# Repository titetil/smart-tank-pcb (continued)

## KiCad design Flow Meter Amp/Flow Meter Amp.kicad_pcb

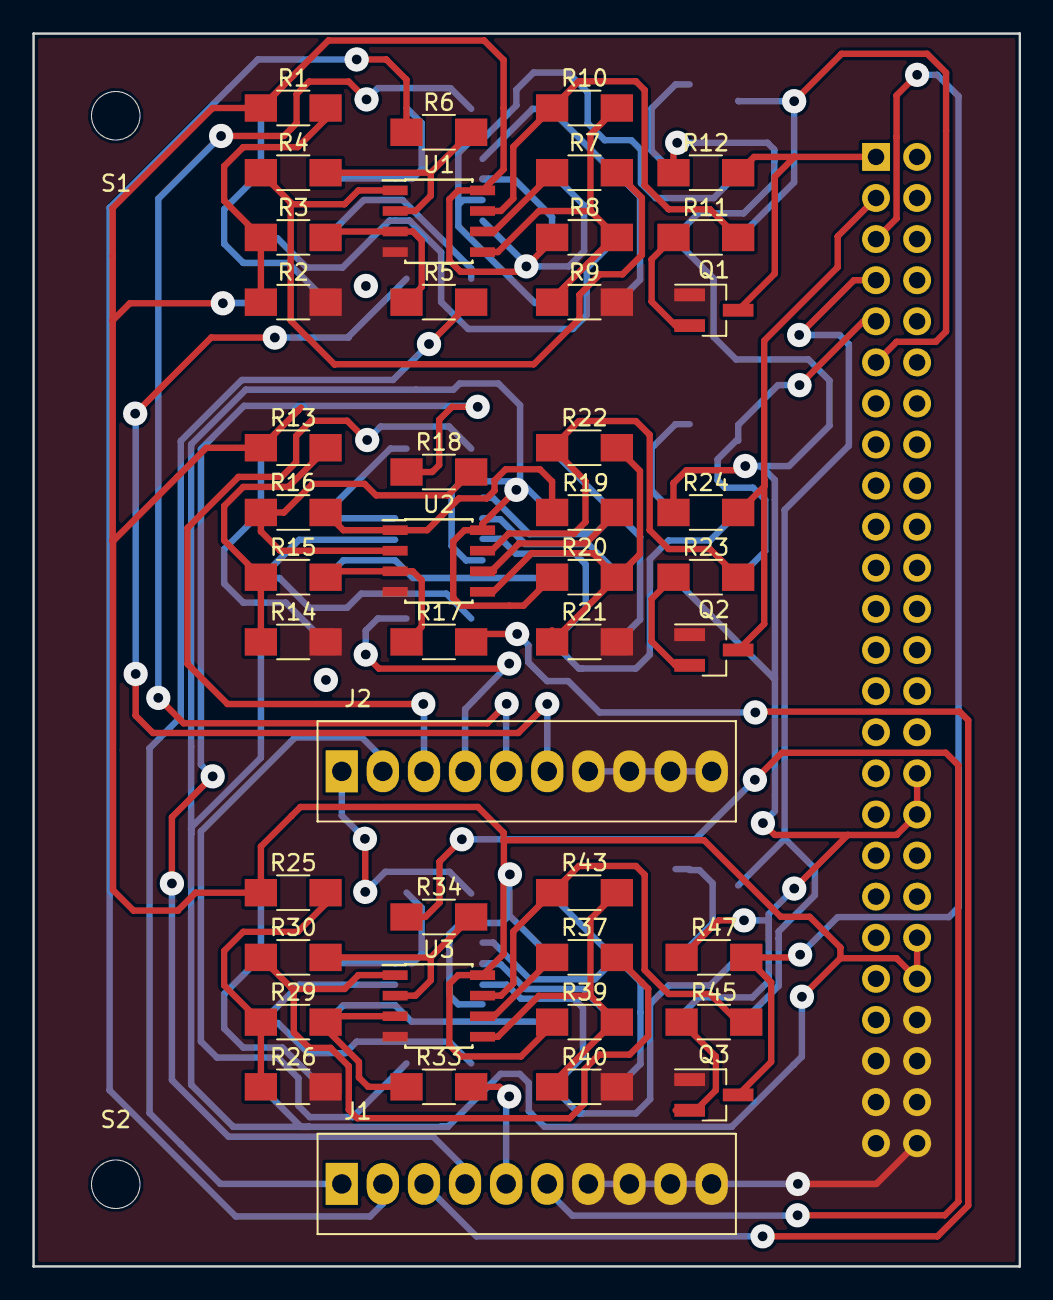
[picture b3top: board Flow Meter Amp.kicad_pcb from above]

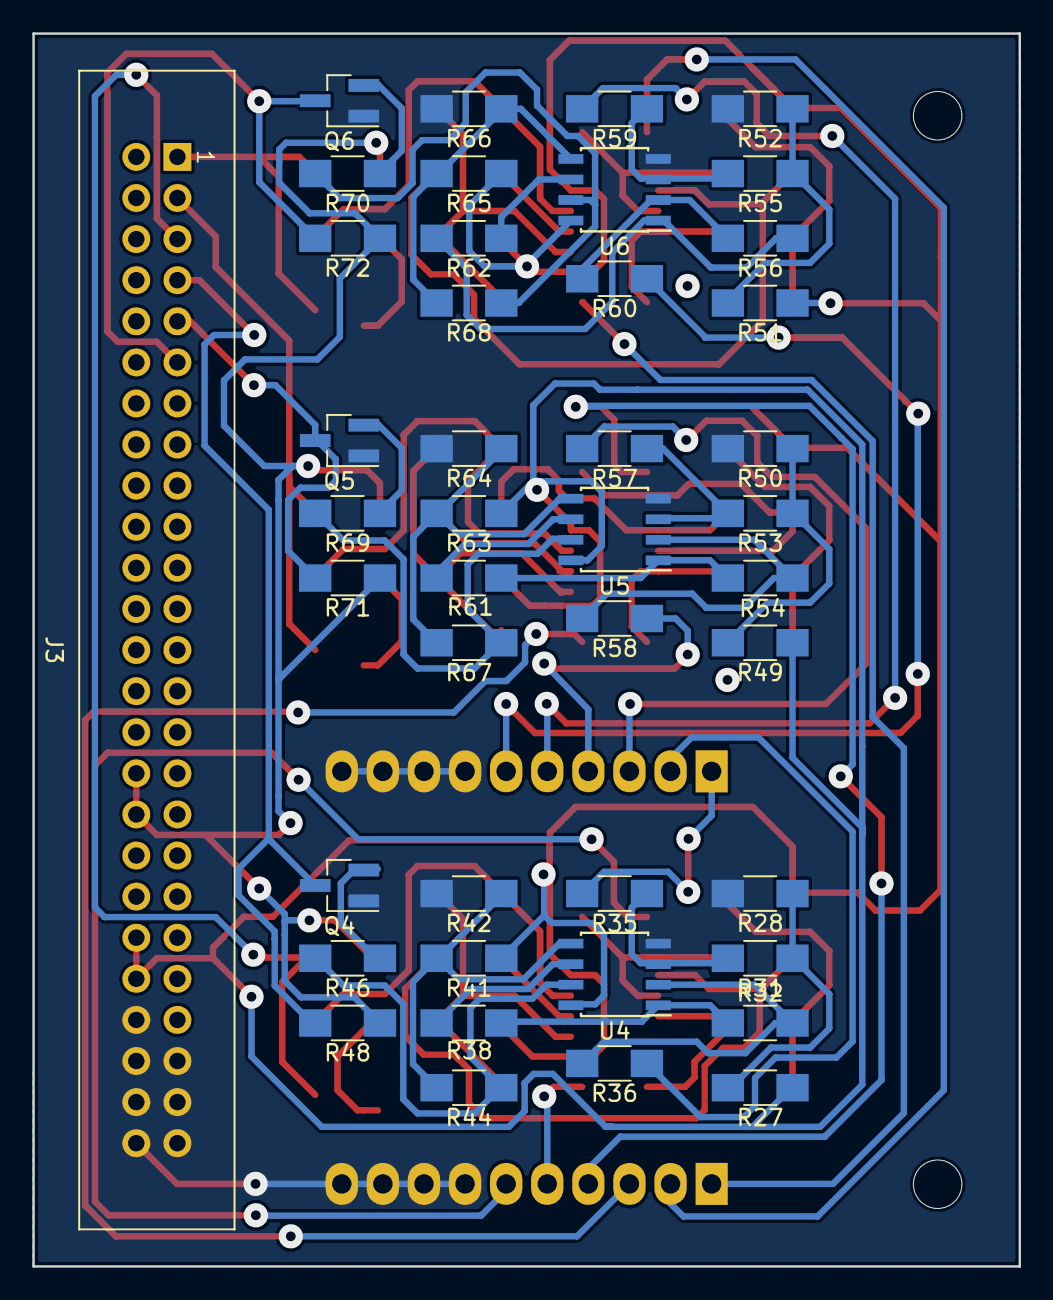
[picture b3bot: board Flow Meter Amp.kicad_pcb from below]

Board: 2 copper layers, 61.0 x 76.2 mm, 89 parts (43 on the bottom side), 69 nets.

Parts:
J1, J2: Screw_Terminal_1x10; PHNX_SCREW_CONN_10_POS_2.54_(1725737)
J3: CONN_02X25; 50_PIN_RECPT_(68683-325LF)
Q1, Q2, Q3, Q4, Q5, Q6: MMBT3904; SOT-23_Handsoldering
R1, R2, R13, R14, R25, R26, R27, R28, R49, R50, R51, R52: 2.2k; R_1206_HandSoldering
R3, R4, R15, R16, R29, R30, R31, R32, R53, R54, R55, R56: 499k; R_1206_HandSoldering
R5, R6, R17, R18, R33, R34, R35, R36, R57, R58, R59, R60: 3.32k; R_1206_HandSoldering
R7, R11, R19, R23, R37, R38, R45, R46, R61, R62, R69, R70: 10k; R_1206_HandSoldering
R8, R9, R20, R21, R39, R40, R41, R42, R63, R64, R65, R66: 100k; R_1206_HandSoldering
R10, R22, R43, R44, R67, R68: 1M; R_1206_HandSoldering
R12, R24, R47, R48, R71, R72: 1.2k; R_1206_HandSoldering
S1, S2: MountingHole_3mm
U1, U2, U3, U4, U5, U6: LM358; SOIC-8_3.9x4.9mm_Pitch1.27mm

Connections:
3.3VDC: J3.32, J3.34, R12.1, R24.1, R47.1, R48.1, R71.1, R72.1
24VDC: J3.40, J3.42, R1.1, R8.1, R13.1, R20.1, R25.1, R27.1, R39.1, R41.1, R49.1, R51.1, R63.1, R65.1, U1.8, U2.8, U3.8, U4.8, U5.8, U6.8
COM: J1.7, J1.8, J1.9, J1.10, J2.7, J2.8, J2.9, J2.10, J3.44, J3.45, J3.46, J3.47, J3.48, J3.49, J3.50, Q1.1, Q2.1, Q3.1, Q4.1, Q5.1, Q6.1, R2.2, R9.2, R14.2, R21.2, R26.2, R28.2, R40.2, R42.2, R50.2, R52.2, R64.2, R66.2, U1.4, U2.4, U3.4, U4.4, U5.4, U6.4
FLOW+_1: J1.1, R5.2
FLOW+_2: J1.3, R17.2
FLOW+_3: J1.5, R33.2
FLOW+_4: J2.1, R35.2
FLOW+_5: J2.3, R57.2
FLOW+_6: J2.5, R59.2
FLOW-_1: J1.2, R6.1
FLOW-_2: J1.4, R18.1
FLOW-_3: J1.6, R34.1
FLOW-_4: J2.2, R36.1
FLOW-_5: J2.4, R58.1
FLOW-_6: J2.6, R60.1
unnamed: Q1.2, R11.1
unnamed: Q2.2, R23.1
unnamed: Q3.2, R45.1
unnamed: Q4.2, R46.1
unnamed: Q5.2, R69.1
unnamed: Q6.2, R70.1
unnamed: R1.2, R2.1, R3.1
unnamed: R3.2, R5.1, U1.3
unnamed: R4.1, R7.2, U1.1
unnamed: R4.2, R6.2, U1.2
unnamed: R7.1, U1.6
unnamed: R10.1, R11.2, U1.7
unnamed: R8.2, R9.1, R10.2, U1.5
unnamed: R13.2, R14.1, R15.1
unnamed: R15.2, R17.1, U2.3
unnamed: R16.1, R19.2, U2.1
unnamed: R16.2, R18.2, U2.2
unnamed: R19.1, U2.6
unnamed: R20.2, R21.1, R22.2, U2.5
unnamed: R22.1, R23.2, U2.7
unnamed: R25.2, R26.1, R29.1
unnamed: R27.2, R28.1, R31.1
unnamed: R29.2, R33.1, U3.3
unnamed: R30.1, R37.2, U3.1
unnamed: R30.2, R34.2, U3.2
unnamed: R31.2, R35.1, U4.3
unnamed: R32.1, R38.2, U4.1
unnamed: R32.2, R36.2, U4.2
unnamed: R37.1, U3.6
unnamed: R38.1, U4.6
unnamed: R39.2, R40.1, R43.2, U3.5
unnamed: R41.2, R42.1, R44.2, U4.5
unnamed: R43.1, R45.2, U3.7
unnamed: R44.1, R46.2, U4.7
unnamed: R49.2, R50.1, R53.1
unnamed: R51.2, R52.1, R55.1
unnamed: R53.2, R57.1, U5.3
unnamed: R54.1, R61.2, U5.1
unnamed: R54.2, R58.2, U5.2
unnamed: R55.2, R59.1, U6.3
unnamed: R56.1, R62.2, U6.1
unnamed: R56.2, R60.2, U6.2
unnamed: R61.1, U5.6
unnamed: R62.1, U6.6
unnamed: R63.2, R64.1, R67.2, U5.5
unnamed: R65.2, R66.1, R68.2, U6.5
unnamed: R67.1, R69.2, U5.7
unnamed: R68.1, R70.2, U6.7
PULSE_OUT_1: J3.1, Q1.3, R12.2
PULSE_OUT_2: J3.3, Q2.3, R24.2
PULSE_OUT_3: J3.5, Q3.3, R47.2
PULSE_OUT_4: J3.7, Q4.3, R48.2
PULSE_OUT_5: J3.9, Q5.3, R71.2
PULSE_OUT_6: J3.11, Q6.3, R72.2

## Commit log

2017-03-30 -finished Flow Meter Amp PCB design. ready to route.
2017-03-31 created gerbers and lmd file.
2017-07-27 - Refer to Google Drive BOM for list of changes for v1.1 - Create drawing for Hella BLDC controller plate.
2017-07-27 - Added board router files back in. They were deleted by accident.
2020-06-10 - Created Modbus Adapter.
2021-07-20 Created Smart Tank Current Shunt PCB, v1.0
2025-11-12 Committing what appears to be a bunch of backup files. Haven't touched this project in a while, so I'm going for it.
2025-11-14 Finished schematic for next version. Need to assign footprints next.
2025-11-17 Schematic ready. Going to clean up directory now.
2025-11-17 Started cleaning out old parts from PCB.
2025-11-18 Continued cleanup and reconnects.
2025-11-19 Almost done with re-routing.
2025-12-01 Almost done with PCB. Tying up a few loose ends.
2025-12-03 Design files were sent out for quote.
2026-02-18 Capacitor part issues...
    Made these changes...
    Concerning C13, C15, C27, C28, C31, C32, C35, C36, C39, C40, C43, C44
    The schematic is wrong, and the BOM is correct. These should all be 0.1uF
    Concerning C20, C21, C29, C30, C33, C34, C37, C38, C41, C42, C45, C46
    The BOM is wrong, and the schematic is correct. These should all be 4.7nF
